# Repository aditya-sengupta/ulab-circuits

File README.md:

# ulab-circuits
Circuitry tutorials for ULAB Physics and Astronomy!

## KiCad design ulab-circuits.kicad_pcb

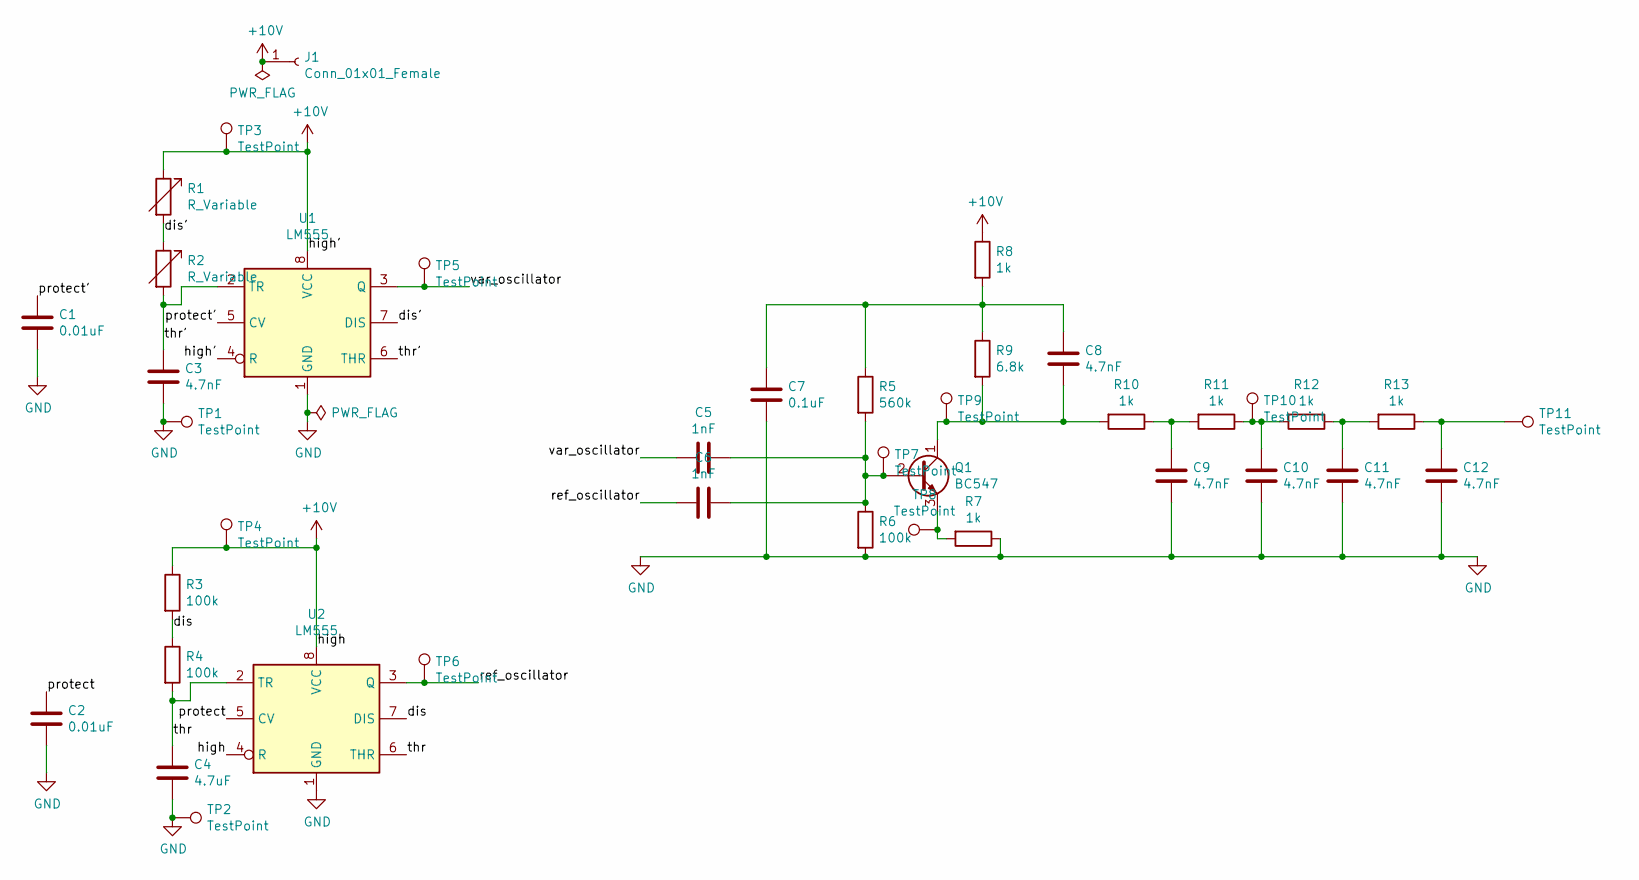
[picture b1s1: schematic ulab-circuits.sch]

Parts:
C1, C2: 0.01uF; C_0805_2012Metric
C3: 4.7nF; C_0402_1005Metric
C4: 4.7uF; C_0402_1005Metric
C5, C6: 1nF; C_0201_0603Metric
C7: 0.1uF; C_0201_0603Metric
C8, C9, C10, C11, C12: 4.7nF; C_0201_0603Metric
J1: Conn_01x01_Female; Banana_Jack_1Pin
Q1: BC547; TO-92_Inline
R1, R2: R_Variable; Potentiometer_Bourns_PTA2043_Single_Slide
R3, R4, R6: 100k; R_0402_1005Metric
R5: 560k; R_Axial_DIN0204_L3.6mm_D1.6mm_P1.90mm_Vertical
R7, R8, R10, R11, R12, R13: 1k; R_0402_1005Metric
R9: 6.8k; R_0805_2012Metric
TP1, TP2, TP3, TP4, TP5, TP6, TP7, TP8, TP9, TP10, TP11: TestPoint; TestPoint_Keystone_5019_Minature
U1, U2: LM555; SOIC127P600X175-8N

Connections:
+10V: J1.1, R1.1, R3.1, R8.1, TP3.1, TP4.1, U1.4 (R), U1.8 (VCC), U2.4 (R), U2.8 (VCC)
/dis: R3.2, R4.1, U2.7 (DIS)
/dis': R1.2, R2.1, U1.7 (DIS)
/protect: C2.1, U2.5 (CV)
/protect': C1.1, U1.5 (CV)
/ref_oscillator: C6.1, TP6.1, U2.3 (Q)
/thr: C4.2, R4.2, U2.2 (TR), U2.6 (THR)
/thr': C3.2, R2.2, U1.2 (TR), U1.6 (THR)
/var_oscillator: C5.1, TP5.1, U1.3 (Q)
GND: C1.2, C2.2, C3.1, C4.1, C7.2, C9.2, C10.2, C11.2, C12.2, R6.2, R7.1, TP1.1, TP2.1, U1.1 (GND), U2.1 (GND)
unnamed: C5.2, C6.2, Q1.2 (B), R5.2, R6.1, TP7.1
unnamed: C7.1, C8.1, R5.1, R8.2, R9.1
unnamed: C8.2, Q1.1 (C), R9.2, R10.2, TP9.1
unnamed: C9.1, R10.1, R11.2
unnamed: C10.1, R11.1, R12.2, TP10.1
unnamed: C11.1, R12.1, R13.2
unnamed: C12.1, R13.1, TP11.1
unnamed: Q1.3 (E), R7.2, TP8.1

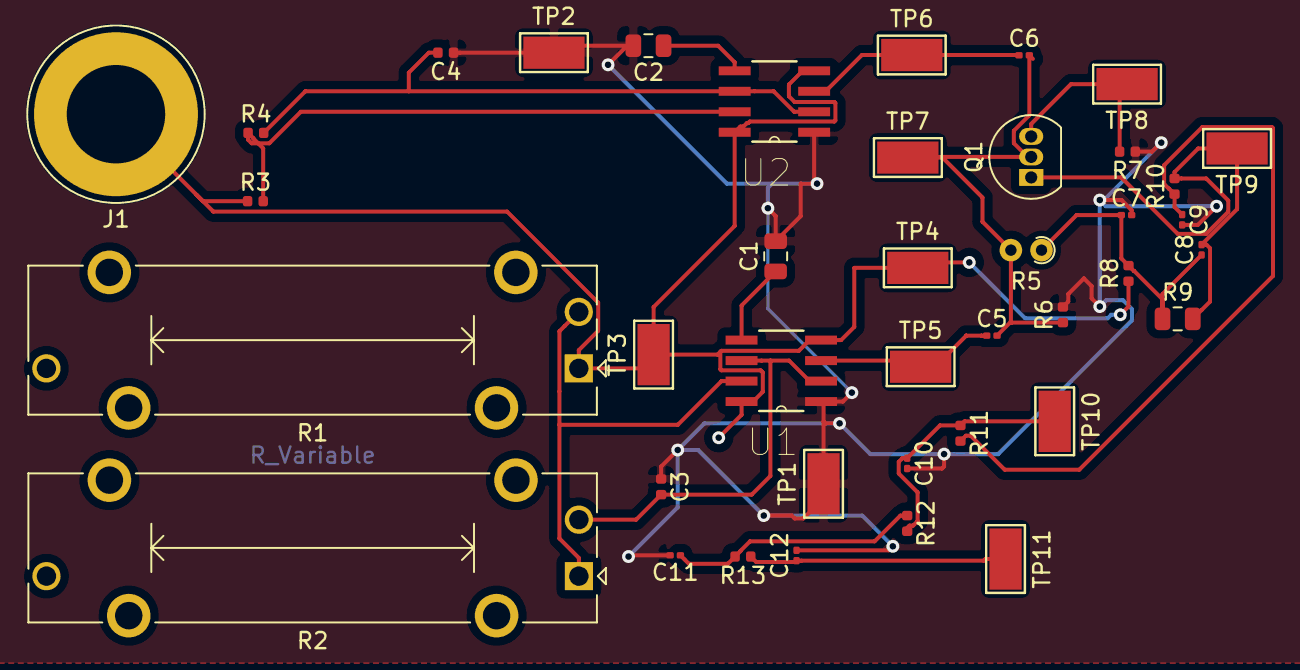
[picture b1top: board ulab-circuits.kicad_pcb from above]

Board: 2 copper layers, 40 parts (0 on the bottom side), 18 nets.

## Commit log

2020-02-10 v1 schematic, v2 unfinished layout
2020-02-10 layout done except grounds and +10Vs
2020-02-10 passed DRC
